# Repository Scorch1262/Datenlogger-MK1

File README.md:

# Datenlogger-MK1

 Funktionen (Software V4.0) [F]:
- MCC UART Funktion
- MCC SPI Funktion
- MCC Flash (SD-Karten) Funktion
- MCC FATfs Funktion
- LED Definiert
- Status LED1 für den Abbruch des schreibvorgangs wegen fehlendem Medium.
- 32MHz
- Erzeugt eine .txt Datei und schreibt Messwerte und eine Zahl hinein
- In einer Endlosscheife immer in der nächsten Zeile
- Auslesen des Sensors (LPS33HW)
- Auslesen des ADCs (MCP3221)
- Auslesen der RTC (MCP79410)
- Schreiben der Werte auf die SD-Karte
  - Schreiben der Daten in Datumsabhängige dateien
  - beibehalten des Richtigen Datums/Uhrzeit

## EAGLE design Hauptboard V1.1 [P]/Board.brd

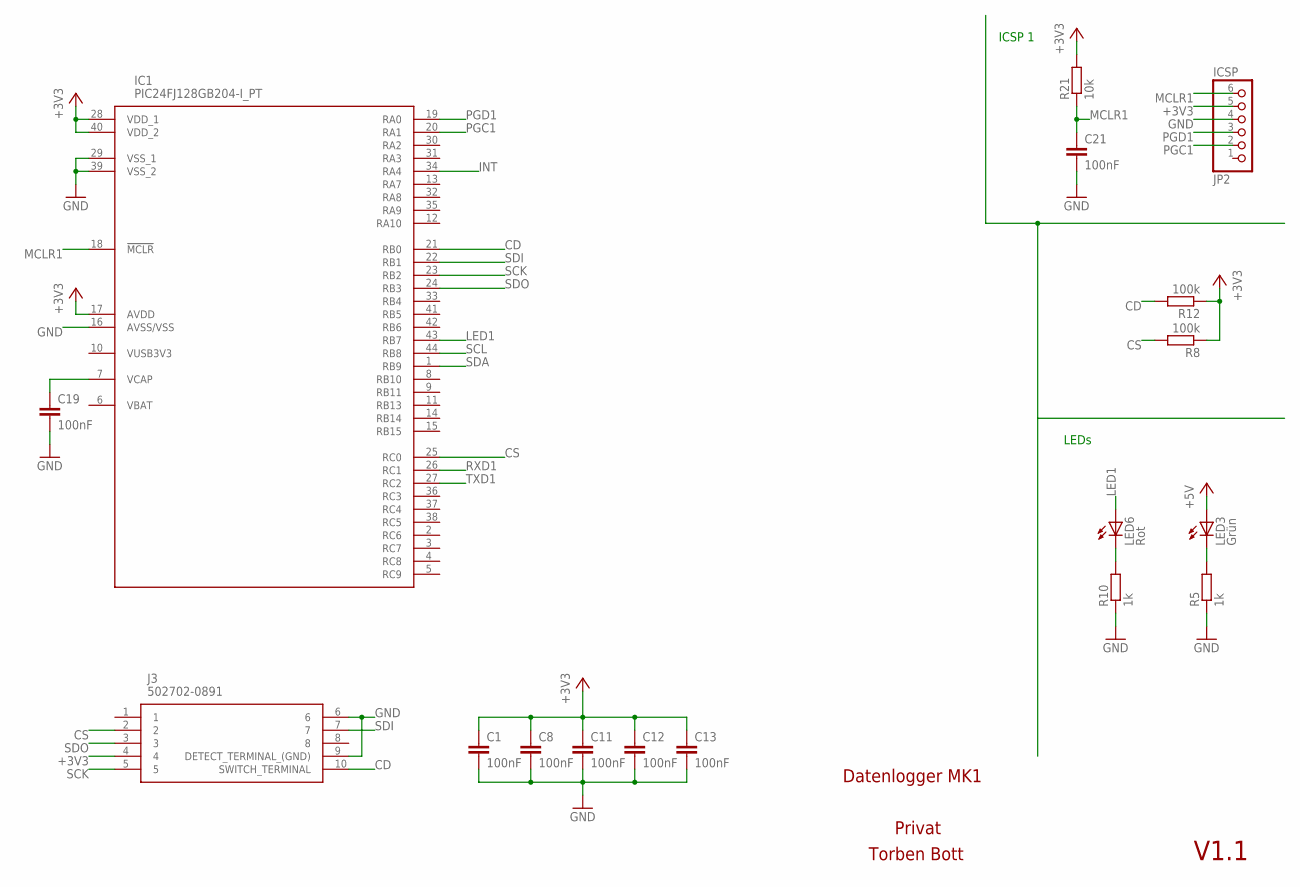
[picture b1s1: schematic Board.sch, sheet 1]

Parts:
C1, C8, C11, C12, C13, C19, C21: 100nF; C0805
IC1: PIC24FJ128GB204-I_PT; QFP80P1200X1200X120-44N
J3: 502702-0891
JP2: ICSP; 1X06/90
LED3: Grün; CHIPLED_0805
LED6: Rot; CHIPLED_0805
R5, R10: 1k; R0805
R8, R12: 100k; R0805
R21: 10k; R0805

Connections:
+3V3: C1.1, C8.1, C11.1, C12.1, C13.1, IC1.17 (AVDD), IC1.28 (VDD_1), IC1.40 (VDD_2), J3.4, JP2.5, R8.1, R12.1, R21.2; also elsewhere on the board
+5V: LED3.A; also elsewhere on the board
CD: IC1.21 (RB0), J3.10 (SWITCH_TERMINAL), R12.2
CS: IC1.25 (RC0), J3.2, R8.2
GND: C1.2, C8.2, C11.2, C12.2, C13.2, C19.2, C21.2, IC1.16 (AVSS/VSS), IC1.29 (VSS_1), IC1.39 (VSS_2), J3.6, J3.9 (DETECT_TERMINAL_(GND)), JP2.4, R5.1, R10.1; also elsewhere on the board
INT: IC1.34 (RA4); also elsewhere on the board
LED1: IC1.43 (RB7), LED6.A
MCLR1: C21.1, IC1.18 (!MCLR), JP2.6, R21.1
unnamed: LED3.C, R5.2
unnamed: LED6.C, R10.2
unnamed: C19.1, IC1.7 (VCAP)
PGC1: IC1.20 (RA1), JP2.2
PGD1: IC1.19 (RA0), JP2.3
RXD1: IC1.26 (RC1)
SCK: IC1.23 (RB2), J3.5
SCL: IC1.44 (RB8); also elsewhere on the board
SDA: IC1.1 (RB9); also elsewhere on the board
SDI: IC1.22 (RB1), J3.7
SDO: IC1.24 (RB3), J3.3
TXD1: IC1.27 (RC2)

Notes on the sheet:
ICSP 1
LEDs
Datenlogger MK1
Privat
Torben Bott
V1.1

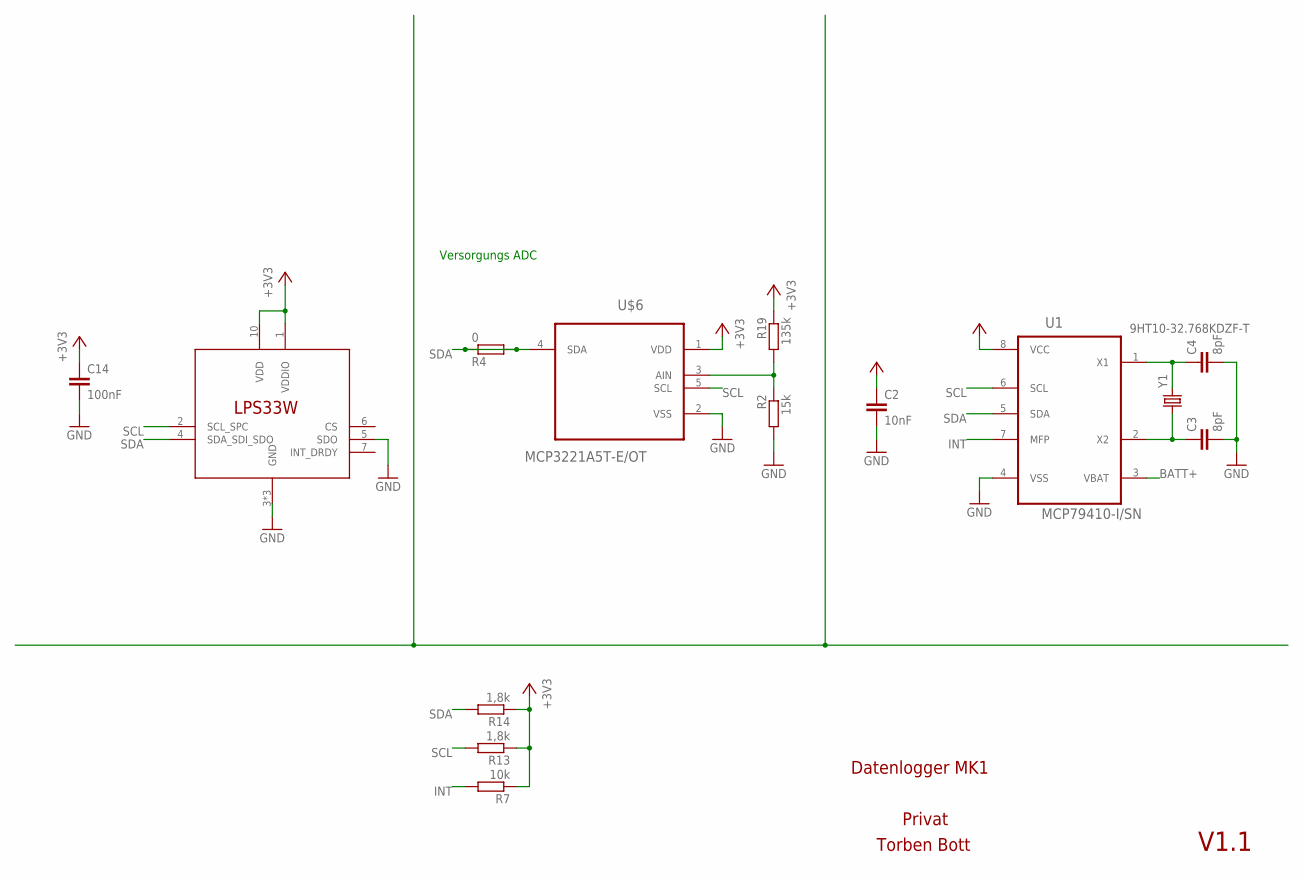
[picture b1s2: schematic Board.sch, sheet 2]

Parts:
C2: 10nF; C0805
C3, C4: 8pF; C0805
C14: 100nF; C0805
R2: 15k; R0805
R4: 0; R0805
R7: 10k; R0805
R13, R14: 1,8k; R0805
R19: 135k; R0805
U1: MCP79410-I/SN; SOIC127P600X175-8N
U$6: MCP3221A5T-E/OT; SOT95P270X145-5N
U$7: LPS33W; CCLGA10L
Y1: 9HT10-32.768KDZF-T; 9HT1032768KEZFT

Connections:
+3V3: C2.1, C14.1, R7.1, R13.1, R14.1, R19.1, U1.8 (VCC), U$6.1 (VDD), U$7.1 (VDDIO), U$7.10 (VDD); also elsewhere on the board
BATT+: U1.3 (VBAT); also elsewhere on the board
GND: C2.2, C3.2, C4.2, C14.2, R2.2, U1.4 (VSS), U$6.2 (VSS), U$7.3 (GND), U$7.5 (SDO), U$7.8 (GND), U$7.9 (GND); also elsewhere on the board
INT: R7.2, U1.7 (MFP); also elsewhere on the board
unnamed: C3.1, U1.2 (X2), Y1.1
unnamed: C4.1, U1.1 (X1), Y1.2
unnamed: R2.1, R19.2, U$6.3 (AIN)
SCL: R13.2, U1.6 (SCL), U$6.5 (SCL), U$7.2 (SCL_SPC); also elsewhere on the board
SDA: R4.1, R4.2, R14.2, U1.5 (SDA), U$6.4 (SDA), U$7.4 (SDA_SDI_SDO); also elsewhere on the board

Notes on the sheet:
Datenlogger MK1
Privat
Torben Bott
Versorgungs ADC
V1.1

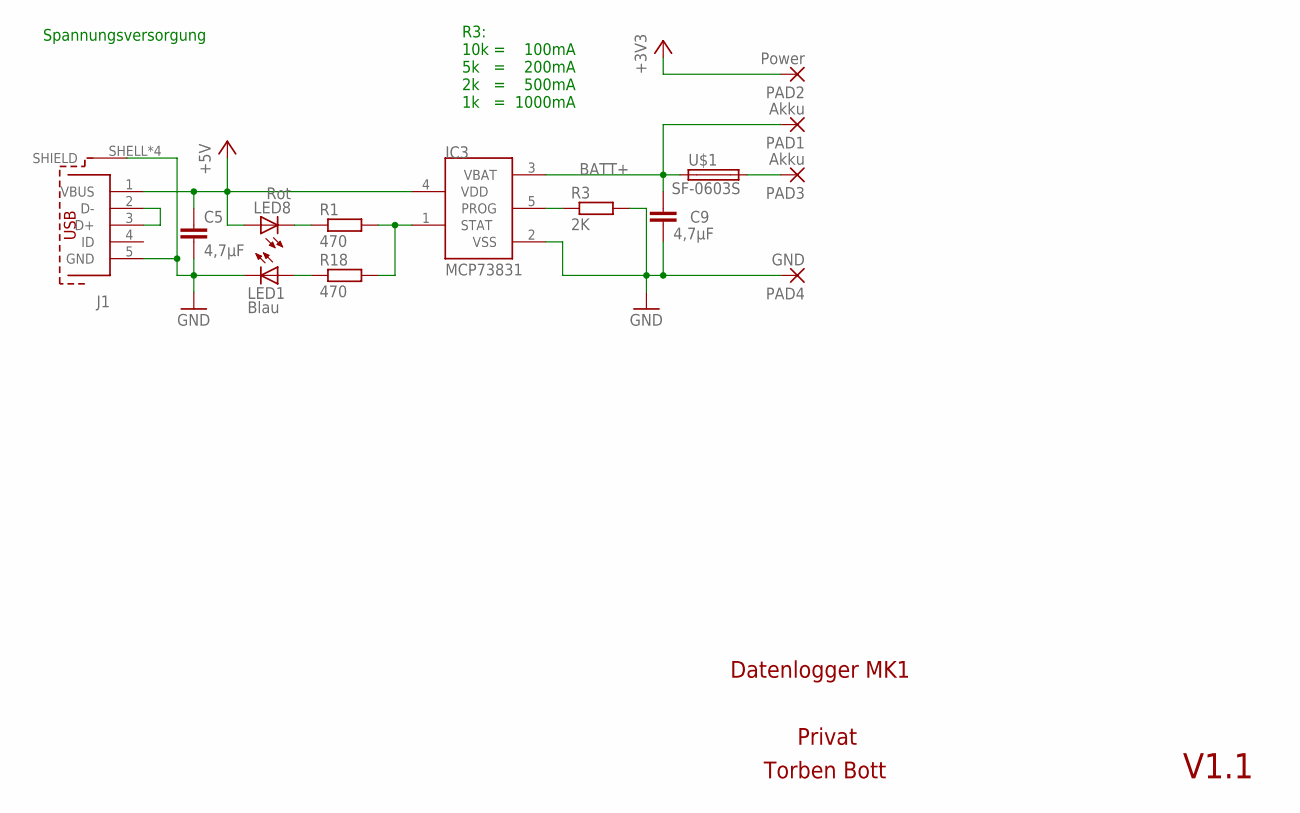
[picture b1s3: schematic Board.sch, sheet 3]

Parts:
C5, C9: 4,7µF; C0805
IC3: MCP73831; SOT23-5L
J1: 629105136821
LED1: Blau; CHIPLED_0805
LED8: Rot; CHIPLED_0805
PAD1, PAD3: Akku; 5-1,8
PAD2: Power; 5-1,8
PAD4: GND; 5-1,8
R1, R18: 470; R0805
R3: 2K; R0805
U$1: SF-0603S; R0603

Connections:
+3V3: PAD2.1; also elsewhere on the board
+5V: C5.1, IC3.4 (VDD), J1.1 (VBUS), LED8.A; also elsewhere on the board
BATT+: C9.1, IC3.3 (VBAT), PAD1.1, U$1.1; also elsewhere on the board
GND: C5.2, C9.2, IC3.2 (VSS), J1.5 (GND), J1.SHELL (SHIELD), J1.SHELL1 (SHIELD), J1.SHELL2 (SHIELD), J1.SHELL3 (SHIELD), LED1.C, PAD4.1, R3.2; also elsewhere on the board
unnamed: LED8.C, R1.1
unnamed: IC3.5 (PROG), R3.1
unnamed: PAD3.1, U$1.2
unnamed: LED1.A, R18.1
unnamed: IC3.1 (STAT), R1.2, R18.2
unnamed: J1.2 (D-), J1.3 (D+)

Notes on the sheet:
Datenlogger MK1
Privat
Torben Bott
Spannungsversorgung
R3: 10k = 100mA 5k = 200mA 2k = 500mA 1k = 1000mA
V1.1

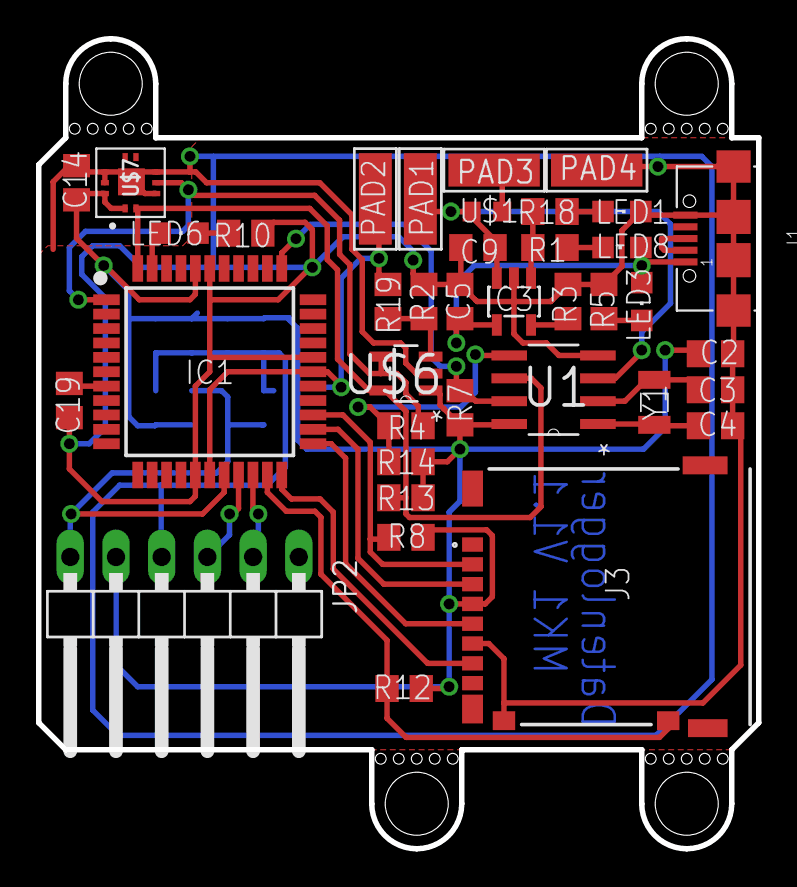
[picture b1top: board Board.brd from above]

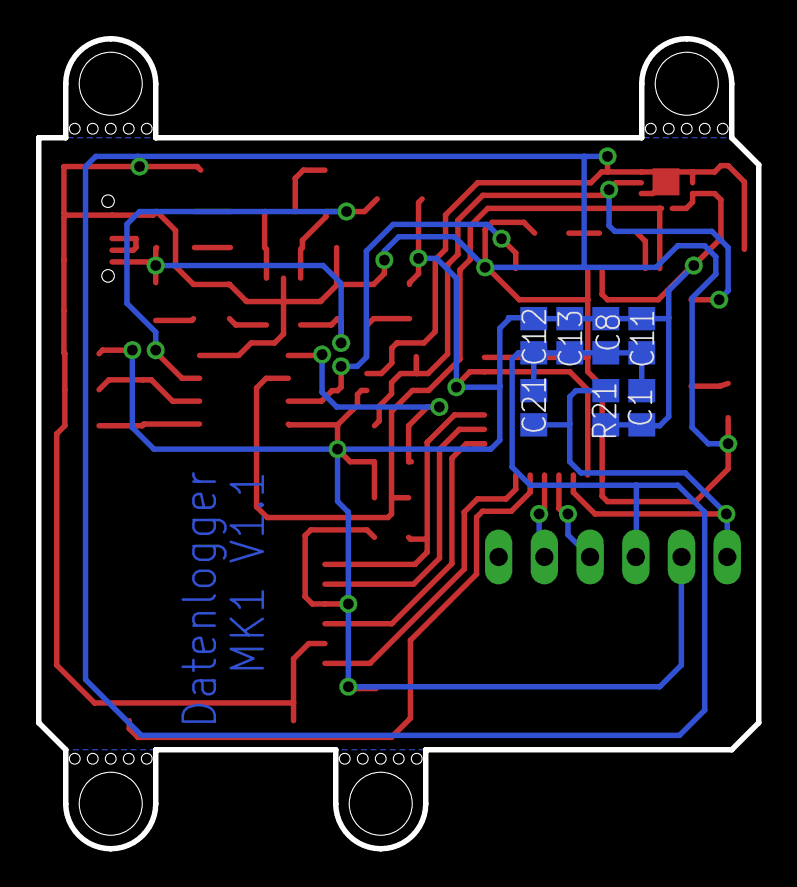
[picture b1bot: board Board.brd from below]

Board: 2 copper layers, 40.0 x 45.0 mm, 45 parts (7 on the bottom side), 28 nets.

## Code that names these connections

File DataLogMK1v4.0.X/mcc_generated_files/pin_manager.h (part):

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*/
/**
  @Summary
    Sets the GPIO pin, RB0, high using LATB0.

  @Description
    Sets the GPIO pin, RB0, high using LATB0.

  @Preconditions
    The RB0 must be set to an output.
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#define SDCard_CD_SetHigh()          (_LATB0 = 1)
/**
  @Summary
    Sets the GPIO pin, RB0, low using LATB0.

  @Description
    Sets the GPIO pin, RB0, low using LATB0.

  @Preconditions
    The RB0 must be set to an output.
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#define SDCard_CD_SetLow()           (_LATB0 = 0)
/**
  @Summary
    Toggles the GPIO pin, RB0, using LATB0.

  @Description
    Toggles the GPIO pin, RB0, using LATB0.

  @Preconditions
    The RB0 must be set to an output.
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#define SDCard_CD_Toggle()           (_LATB0 ^= 1)
/**
  @Summary
    Reads the value of the GPIO pin, RB0.

  @Description
    Reads the value of the GPIO pin, RB0.

  @Preconditions
    None.
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    </code>

*/
#define SDCard_CD_GetValue()         _RB0
/**
  @Summary
    Configures the GPIO pin, RB0, as an input.

  @Description
    Configures the GPIO pin, RB0, as an input.

  @Preconditions
    None.
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#define SDCard_CD_SetDigitalInput()  (_TRISB0 = 1)
/**
  @Summary
    Configures the GPIO pin, RB0, as an output.

  @Description
    Configures the GPIO pin, RB0, as an output.

  @Preconditions
    None.
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#define SDCard_CD_SetDigitalOutput() (_TRISB0 = 0)
/**
  @Summary
    Sets the GPIO pin, RB1, high using LATB1.

  @Description
    Sets the GPIO pin, RB1, high using LATB1.

  @Preconditions
    The RB1 must be set to an output.
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#define SDI1_SetHigh()          (_LATB1 = 1)
/**
  @Summary
    Sets the GPIO pin, RB1, low using LATB1.

  @Description
    Sets the GPIO pin, RB1, low using LATB1.

  @Preconditions
    The RB1 must be set to an output.
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#define SDI1_SetLow()           (_LATB1 = 0)
/**
  @Summary
    Toggles the GPIO pin, RB1, using LATB1.

  @Description
    Toggles the GPIO pin, RB1, using LATB1.

  @Preconditions
    The RB1 must be set to an output.
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#define SDI1_Toggle()           (_LATB1 ^= 1)
/**
  @Summary
    Reads the value of the GPIO pin, RB1.

  @Description
    Reads the value of the GPIO pin, RB1.

  @Preconditions
    None.
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    </code>

*/
#define SDI1_GetValue()         _RB1
/**
  @Summary
    Configures the GPIO pin, RB1, as an input.

  @Description
    Configures the GPIO pin, RB1, as an input.

  @Preconditions
    None.
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#define SDI1_SetDigitalInput()  (_TRISB1 = 1)
/**
  @Summary
    Configures the GPIO pin, RB1, as an output.

  @Description
    Configures the GPIO pin, RB1, as an output.

  @Preconditions
    None.
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#define SDI1_SetDigitalOutput() (_TRISB1 = 0)
/**
  @Summary
    Sets the GPIO pin, RB2, high using LATB2.

  @Description
    Sets the GPIO pin, RB2, high using LATB2.

  @Preconditions
    The RB2 must be set to an output.
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#define SCK1OUT_SetHigh()          (_LATB2 = 1)
/**
  @Summary
    Sets the GPIO pin, RB2, low using LATB2.

  @Description
    Sets the GPIO pin, RB2, low using LATB2.

  @Preconditions
    The RB2 must be set to an output.
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#define SCK1OUT_SetLow()           (_LATB2 = 0)
/**
  @Summary
    Toggles the GPIO pin, RB2, using LATB2.

  @Description
    Toggles the GPIO pin, RB2, using LATB2.

  @Preconditions
    The RB2 must be set to an output.
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#define SCK1OUT_Toggle()           (_LATB2 ^= 1)
/**
  @Summary
    Reads the value of the GPIO pin, RB2.

  @Description
    Reads the value of the GPIO pin, RB2.

  @Preconditions
    None.
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    </code>

*/
#define SCK1OUT_GetValue()         _RB2
/**
  @Summary
    Configures the GPIO pin, RB2, as an input.

  @Description
    Configures the GPIO pin, RB2, as an input.

  @Preconditions
    None.
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#define SCK1OUT_SetDigitalInput()  (_TRISB2 = 1)
/**
  @Summary
    Configures the GPIO pin, RB2, as an output.

  @Description
    Configures the GPIO pin, RB2, as an output.

  @Preconditions
    None.
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#define SCK1OUT_SetDigitalOutput() (_TRISB2 = 0)
/**
  @Summary
    Sets the GPIO pin, RB3, high using LATB3.

  @Description
    Sets the GPIO pin, RB3, high using LATB3.

  @Preconditions
    The RB3 must be set to an output.
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#define SDO1_SetHigh()          (_LATB3 = 1)
/**
  @Summary
    Sets the GPIO pin, RB3, low using LATB3.

  @Description
    Sets the GPIO pin, RB3, low using LATB3.

  @Preconditions
    The RB3 must be set to an output.
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#define SDO1_SetLow()           (_LATB3 = 0)
/**
  @Summary
    Toggles the GPIO pin, RB3, using LATB3.

  @Description
    Toggles the GPIO pin, RB3, using LATB3.

  @Preconditions
    The RB3 must be set to an output.
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#define SDO1_Toggle()           (_LATB3 ^= 1)
/**
  @Summary
    Reads the value of the GPIO pin, RB3.

  @Description
    Reads the value of the GPIO pin, RB3.

  @Preconditions
    None.
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    </code>

*/
#define SDO1_GetValue()         _RB3
/**
  @Summary
    Configures the GPIO pin, RB3, as an input.

  @Description
    Configures the GPIO pin, RB3, as an input.

  @Preconditions
    None.
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#define SDO1_SetDigitalInput()  (_TRISB3 = 1)
/**
  @Summary
    Configures the GPIO pin, RB3, as an output.

  @Description
    Configures the GPIO pin, RB3, as an output.

  @Preconditions
    None.
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#define SDO1_SetDigitalOutput() (_TRISB3 = 0)
/**
  @Summary
    Sets the GPIO pin, RB7, high using LATB7.

  @Description
    Sets the GPIO pin, RB7, high using LATB7.

  @Preconditions
    The RB7 must be set to an output.
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#define LED1_SetHigh()          (_LATB7 = 1)
/**
  @Summary
    Sets the GPIO pin, RB7, low using LATB7.

  @Description
    Sets the GPIO pin, RB7, low using LATB7.

  @Preconditions
    The RB7 must be set to an output.
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#define LED1_SetLow()           (_LATB7 = 0)
/**
  @Summary
    Toggles the GPIO pin, RB7, using LATB7.

  @Description
    Toggles the GPIO pin, RB7, using LATB7.

  @Preconditions
    The RB7 must be set to an output.
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#define LED1_Toggle()           (_LATB7 ^= 1)
/**
  @Summary
    Reads the value of the GPIO pin, RB7.

  @Description
    Reads the value of the GPIO pin, RB7.

  @Preconditions
    None.
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    </code>

*/
#define LED1_GetValue()         _RB7
/**
  @Summary
    Configures the GPIO pin, RB7, as an input.

  @Description
    Configures the GPIO pin, RB7, as an input.

  @Preconditions
    None.
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#define LED1_SetDigitalInput()  (_TRISB7 = 1)
/**
  @Summary
    Configures the GPIO pin, RB7, as an output.

  @Description
    Configures the GPIO pin, RB7, as an output.

  @Preconditions
    None.
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#define LED1_SetDigitalOutput() (_TRISB7 = 0)
/**
  @Summary
    Sets the GPIO pin, RC0, high using LATC0.

  @Description
    Sets the GPIO pin, RC0, high using LATC0.

  @Preconditions
    The RC0 must be set to an output.
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#define SDCard_CS_SetHigh()          (_LATC0 = 1)
/**
  @Summary
    Sets the GPIO pin, RC0, low using LATC0.

  @Description
    Sets the GPIO pin, RC0, low using LATC0.

  @Preconditions
    The RC0 must be set to an output.
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#define SDCard_CS_SetLow()           (_LATC0 = 0)
/**
  @Summary
    Toggles the GPIO pin, RC0, using LATC0.

  @Description
    Toggles the GPIO pin, RC0, using LATC0.

  @Preconditions
    The RC0 must be set to an output.
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#define SDCard_CS_Toggle()           (_LATC0 ^= 1)
/**
  @Summary
    Reads the value of the GPIO pin, RC0.

  @Description
    Reads the value of the GPIO pin, RC0.

  @Preconditions
    None.
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    </code>

*/
#define SDCard_CS_GetValue()         _RC0
/**
  @Summary
    Configures the GPIO pin, RC0, as an input.

  @Description
    Configures the GPIO pin, RC0, as an input.

  @Preconditions
    None.
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#define SDCard_CS_SetDigitalInput()  (_TRISC0 = 1)
/**
  @Summary
    Configures the GPIO pin, RC0, as an output.

  @Description
    Configures the GPIO pin, RC0, as an output.

  @Preconditions
    None.
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

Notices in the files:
DataLogMK1v4.0.X/mcc_generated_files/pin_manager.h:
(c) 2020 Microchip Technology Inc. and its subsidiaries. You may use this
parts and their libraries:
InputOutputIO: Copyright: Würth Elektronik
microbuilder: This work is placed in the public domain, and may be freely used for commercial and non-commercial work with the following conditions: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
